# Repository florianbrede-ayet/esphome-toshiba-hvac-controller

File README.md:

# ESPHome Toshiba / Carrier HVAC Controller over UART / WIFI Interface
This repository contains both the hardware (kicad & production files) for an ESP32 module as well as an [ESPHome](https://esphome.io/) component to control Toshiba / Carrier RAS HVAC units independently from the Toshiba Cloud.

ESP8266 is also supported but requires custom wiring.

The device can be used as a local, low cost drop in replacement to control the AC from [Home Assistant](https://www.home-assistant.io/) or others.

Features of the component:
* All operation modes & fan modes supported
* Does not depend on external vendor cloud services
* External temperature sensor support for accurate temperature regulation (external sensor entity configurable)
* Wired and IR remotes still work, even with external temperature sensor
* Supports most special modes / merit modes like silent, fireplace, extended heating temperature range
* Support for power modes on single split units and ionizer toggle
* Additional information like fan speeds, compressor load, refrigerant / pipe temperatures
* WiFi LED toggle (on/off via UART registers 0xDE/0xDF)

Missing functionality:
* Manual defrost (probably unsupported over UART WIFI interface)
* ODU error messages (not decoded yet)
* Timer / schedules (had no interest in this functionality)
* Capability detection (all fan & merit modes will be shown, but not all might have an effect depending on the IDU)

Requirements:
* Toshiba/Carrier RAS single- or multisplit unit with built-in WIFI interface or WIFI module support (others might work as well, but untested)
* ESP32 DevKit 38 Pins (others like NodeMCU 8266 work as well but might require modifications)
* Toshiba HVAC module (see `hardware/` directory)
* ESPhome installed to flash the ESP32 initially

# UART Protocol
The IDU communicates over 5V `UART 9600E1`.
Messages include a length and a distinct header. Initial synchronization is ensured with a 200ms message timeout.

The protocol is relatively simple and can be observed in the `process_uart_rx` and `handle_message` functions, where the message type is identified by its length.
I've decoded most of the protocol by reading the communication with stock WRE-T00BJ10 modules and analyzing the messages against known responses from the Toshiba Cloud.

We can request registers from the IDU, we can write certain registers and also the IDU will send registers if updated externally (IDU / ODU status and changes via IR remote).

# Compatibility
Probably all Toshiba RAS units with wifi capabilities (built-in or with additional module) are supported.

The software has been tested with the following outdoor units:
* RAS-3M18U2AVG-E (Tripe-split)
* RAS-2M14U2AVG-E (Dual-split)
* RAS-25G2KVP-ND (Single-split)
And these indoor units:
* RAS-B10N4KVRG-E (Haori)
* RAS-25G2AVP-ND (Super DAISEIKAI 8)

Other units (with any compatible outdoor unit) that are almost certainly supported:
* Toshiba Seiya
* Toshiba Shorai
* Rebranded models like *Carrier X Inverter*

# Hardware

The hardware needs three main components:
1) **Microcontroller**. Any ESP32-DevKit with 38 Pins should work. ESP8266 is also supported, see "ESP8266" below.
2) **Bidirectional Voltage Level Translator**. This is needed to connect to the UART interface and shift between 5V from the AC to 3.3V of the ESP32. I used a `Texas Instruments TXS0108EPWR`.
3) **Connector** Toshiba uses as JST PASK connector for the WIFI modules cable, `JST S05B-PASK-2(LF)(SN)` is the correct connector. 

External voltage regulators are not required, as the UART inteface in the indoor units works at 5V and can be directly fed into the ESP32 DevKit.

The Kicad 7 project files and ready-to-use production files (for JLCPCB or PcbWay manufacturing) are available in `hardware/` and `hardware/production` respectively.

*Attention: The Haori units with built-in WIFI modules lack height for the 2x 19p 2.54mm pin sockets. I disabled placement for the pin sockets and soldered the ESP32 on the modules:* 

# Installation
This depends on the indoor unit.
The following photos from a Toshiba Haori show how the built-in module can be replaced in a few minutes:

# Firmware

## ESPHome 2024+ (recommended)

The `toshiba_controller/` directory contains an `external_components`-based component compatible with ESPHome 2024.x and later. The legacy `platform: custom` approach no longer compiles on current ESPHome versions.

> **Note:** ESPHome 2026.5.0 removed the deprecated `ClimateTraits::set_supports_*` accessors in favor of `add_feature_flags()`/`has_feature_flags()`. This component has been updated accordingly and is compatible with ESPHome 2026.5.0 and later (as well as 2024.x/2025.x).

To use the component:
1. Clone this repository and navigate to the `esphome` directory.
2. Install ESPHome: https://esphome.io/guides/installing_esphome.html
3. Copy `template_v3.yaml` to (for example) `toshiba-livingroom.yaml` and fill in your WiFi credentials, API key, and temperature sensor entity ID.
4. Connect the ESP32 module via USB (first flash only; subsequent updates use OTA).
5. Run `esphome run toshiba-livingroom.yaml`.
6. Add the device in Home Assistant (Settings → Devices & Services).

## Migrating from Legacy (`base.yaml` / `platform: custom`)

If you are upgrading from the old `base.yaml` include with `platform: custom`, the main changes are:

1. **Remove the `<<: !include base.yaml`** line and the `includes: [toshiba-controller.h]` reference.
2. **Add `external_components`** pointing to the `toshiba_controller/` directory (see `template_v3.yaml`).
3. **Replace the `climate: platform: custom` block** with a top-level `toshiba_controller:` block.
4. **Replace `sensor: platform: custom`** with `sensor: platform: toshiba_controller` (sensor names are preserved).
5. **Replace `switch: platform: custom`** with `switch: platform: toshiba_controller` for Internal Thermistor and Ionizer.
6. **Split the Special Mode select** into three separate selects: Special Mode, Silent Mode, and Fireplace (the old config had all modes in a single flat list).
7. **Optionally add** the new WiFi LED template switch.

See `template_v3.yaml` for a complete example of the new configuration format.

## Legacy ESPHome (< 2024)

If you are still on an older ESPHome version, use `template.yaml` with the single-file `toshiba-controller.h` from an [older release](https://github.com/florianbrede-ayet/esphome-toshiba-hvac-controller/tree/90621ac). Note that `platform: custom` has been removed in ESPHome 2024.

## Logs

```bash
esphome logs toshiba-livingroom.yaml
```

# ESP8266
ESP8266 is supported but requires custom wiring. Use `template_v3.yaml` as a starting point and adjust the board, UART pins (`GPIO1` TX / `GPIO3` RX), and framework accordingly.
A bidirectional logic level converter must be connected to the UART pins.

The NodeMCU can be powered directly from the indoor unit's UART connector 5V Pin 3 through VIN.

# FAQ
## Smart Thermostat / Internal Thermistor
If the binary switch `Internal Thermistor` is disabled in Home Assistant, the external temperature sensor supplied in the `yaml` configuration will be used for the room temperature.

Most ACs suffer from poor thermistor placement (high position, heat draft) and Toshiba does not support external thermistors over UART.

This requires a more complex regulation in the `smart_thermostat_control` function which can be fine tuned with the `smart_thermostat_multiplier` config parameter.

A recommended value is `4`, which results in a regulation accuracy of around `+/- 0.25°K`.
Higher values increase the accuracy at the cost of more compressor cycles.

## ODU parameters (`cduIac` & `cduLoad`)
The parameters `cduIac` and `cduLoad` seem off at first however, the values are identical to Toshiba's own parameters.

The `cduLoad` is internally called `cduCompHz` by Toshiba and has a range from 0-170.
Since the value has an identical range regardless of the compressor, does not match the actual compressor frequency and is independant for each indoor unit, I converted the number to a percentage which correlates well with the requested power for the IDU.

The same is true for `cduIac` which is closely following `cduLoad`.
My best guess is that `cduLoad` is the heat request for the IDU and `cduIac` is related to the IDU's EEV.

# Credits
* Inspiration & initial protocol description from [ToshibaCarrierHvac](https://github.com/ormsport/ToshibaCarrierHvac)
* ESPhome component structure from [esphome-lg-controller](https://github.com/JanM321/esphome-lg-controller)

# License

This project is released under the MIT License.

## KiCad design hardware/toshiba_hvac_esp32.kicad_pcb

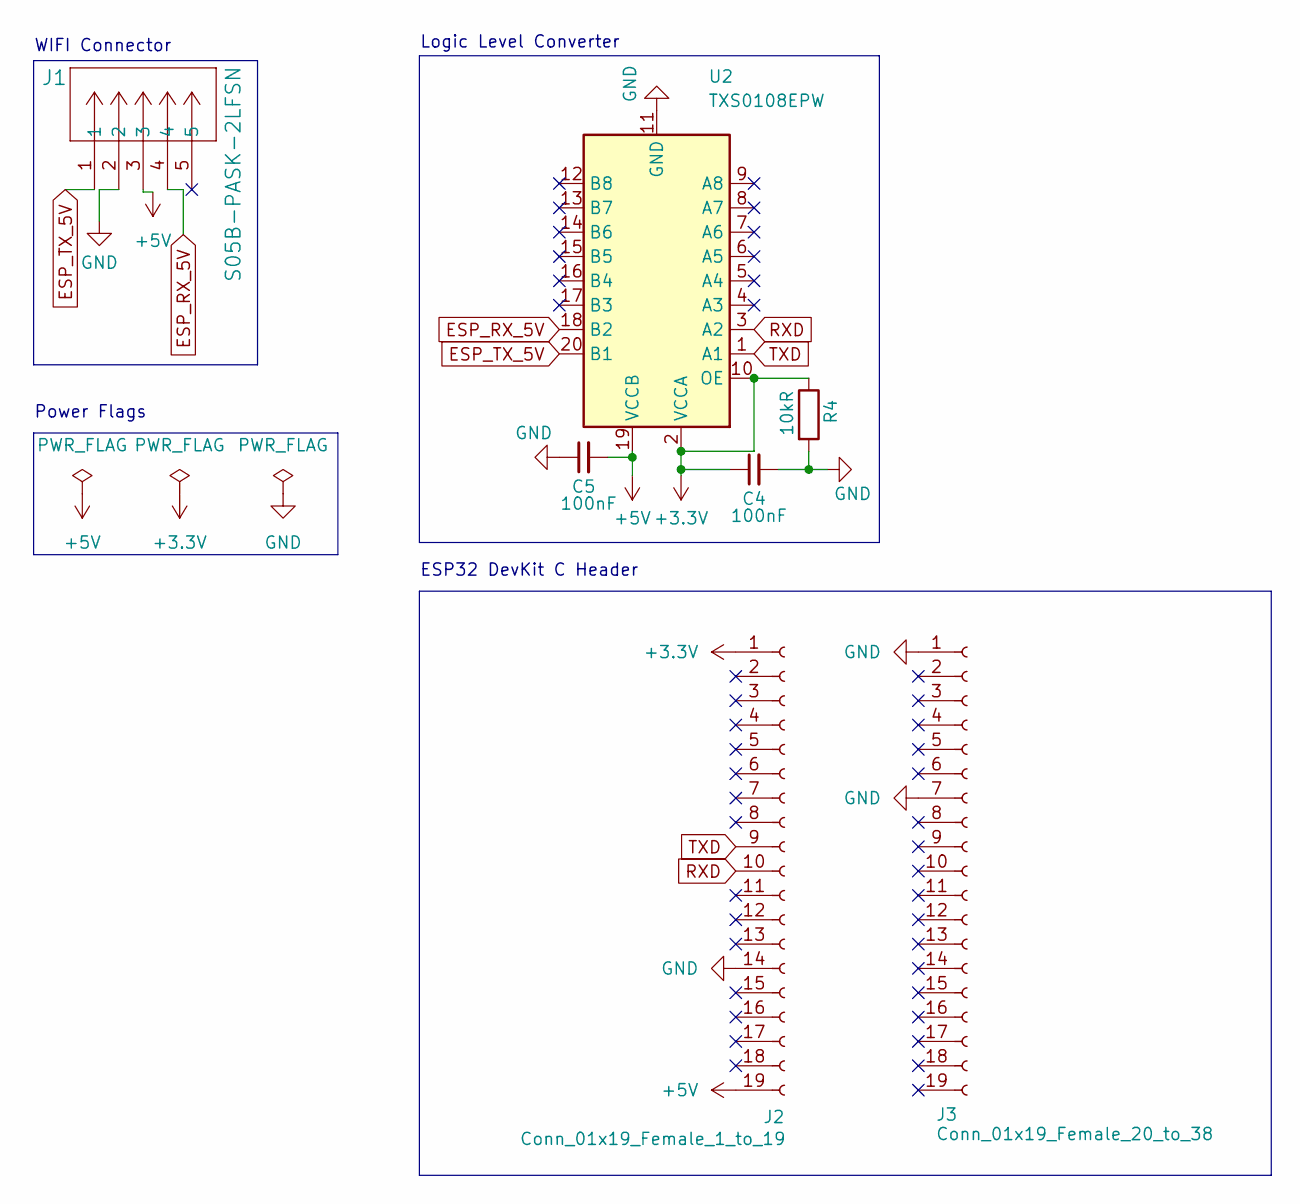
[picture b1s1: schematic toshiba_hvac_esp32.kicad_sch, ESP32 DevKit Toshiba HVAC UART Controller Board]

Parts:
C4, C5: 100nF; C_0402_1005Metric; LCSC C1525
J1: S05B-PASK-2LFSN; CONN_S05B-PASK-2_JST; LCSC C489718
J2: Conn_01x19_Female_1_to_19; PinSocket_1x19_P2.54mm_Vertical; LCSC C2932678
J3: Conn_01x19_Female_20_to_38; PinSocket_1x19_P2.54mm_Vertical; LCSC C2932678
R4: 10kR; R_0603_1608Metric; LCSC C25804
U2: TXS0108EPW; TSSOP-20_4.4x6.5mm_P0.65mm; LCSC C17206

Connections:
+3.3V: C4.1, J2.1, R4.1, U2.2 (VCCA), U2.10 (OE)
+5V: C5.2, J1.3, J2.19, U2.19 (VCCB)
ESP_RX_5V: J1.4, U2.18 (B2)
ESP_TX_5V: J1.1, U2.20 (B1)
GND: C4.2, C5.1, J1.2, J2.14, J3.1, J3.7, R4.2, U2.11 (GND)
RXD: J2.10, U2.3 (A2)
TXD: J2.9, U2.1 (A1)

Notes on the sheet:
WIFI Connector
Logic Level Converter
Power Flags
ESP32 DevKit C Header

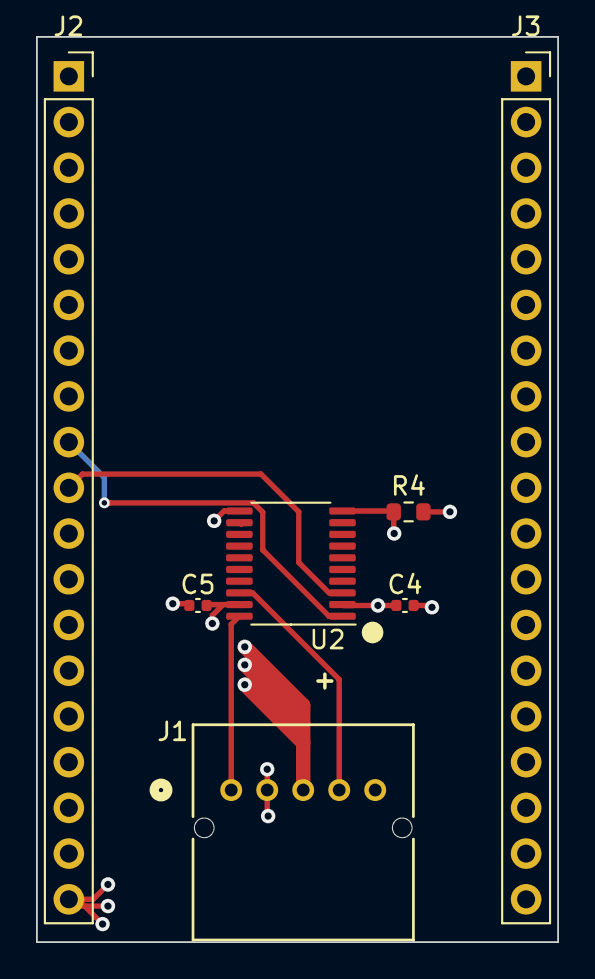
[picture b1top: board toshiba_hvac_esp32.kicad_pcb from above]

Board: 4 copper layers, 29.0 x 50.3 mm, 7 parts (0 on the bottom side), 7 nets.

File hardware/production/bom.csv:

Designator,Footprint,Quantity,Value,LCSC Part #
"C4, C5",0402,2,100nF,C1525
J1,CONN_S05B-PASK-2_JST,1,S05B-PASK-2LFSN,C489718
J2,PinSocket_1x19_P2.54mm_Vertical,1,Conn_01x19_Female_1_to_19,C2932678
J3,PinSocket_1x19_P2.54mm_Vertical,1,Conn_01x19_Female_20_to_38,C2932678
R4,0603,1,10kR,C25804
U2,TSSOP-20_4.4x6.5mm_P0.65mm,1,TXS0108EPW,C17206

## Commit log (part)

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2024-01-29 typo
2024-02-11 implemented an optional "thermal_runaway_protection" flag which shifts the setpoint significantly if the unit does not properly respond to fcu setpoint commands
2024-02-23 Adds base8266.yaml for esp8266 setup, fixes logging
    * Include base8266.yaml instead of base.yaml for 8266 setup
    * Fixed compilation issue
2024-05-08 updated README.md with ESP8266 information
2024-05-08 fixed possible uint8 over/underflows that could cause thermal runaway
2024-12-15 Updated "ota:" example config entry
2025-03-10 fixed bug in external temperature changes (IR remote) with external temperature sensor: - external change messages are ignored - smart thermostat handling and 10s polling for current target temperatu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
2025-03-16 fixed incorrect ECO mode spelling in publish_state (thanks to Kryobot)
2025-10-12 Update internal_power_state when climate mode changes
    Update internal_power_state when climate mode changes in order to react faster to commands after changing modes (e.g. change fan speed or swing mode)
2026-03-11 Add ESPHome 2024+ external_components support with WiFi LED control
    - Add toshiba_controller/ as a proper ESPHome external_components component
    (replaces deprecated platform: custom from template.yaml)
    - climate.py: codegen for all config options (sensors, selects, settings)
    - toshiba_controller.h: fix 5 C++ bugs from original, use constexpr string
    constants, remove deprecated #include "esphome.h", add proper includes
    - Add WiFi LED switch (UART registers 0xDE/0xDF) — was listed as missing
